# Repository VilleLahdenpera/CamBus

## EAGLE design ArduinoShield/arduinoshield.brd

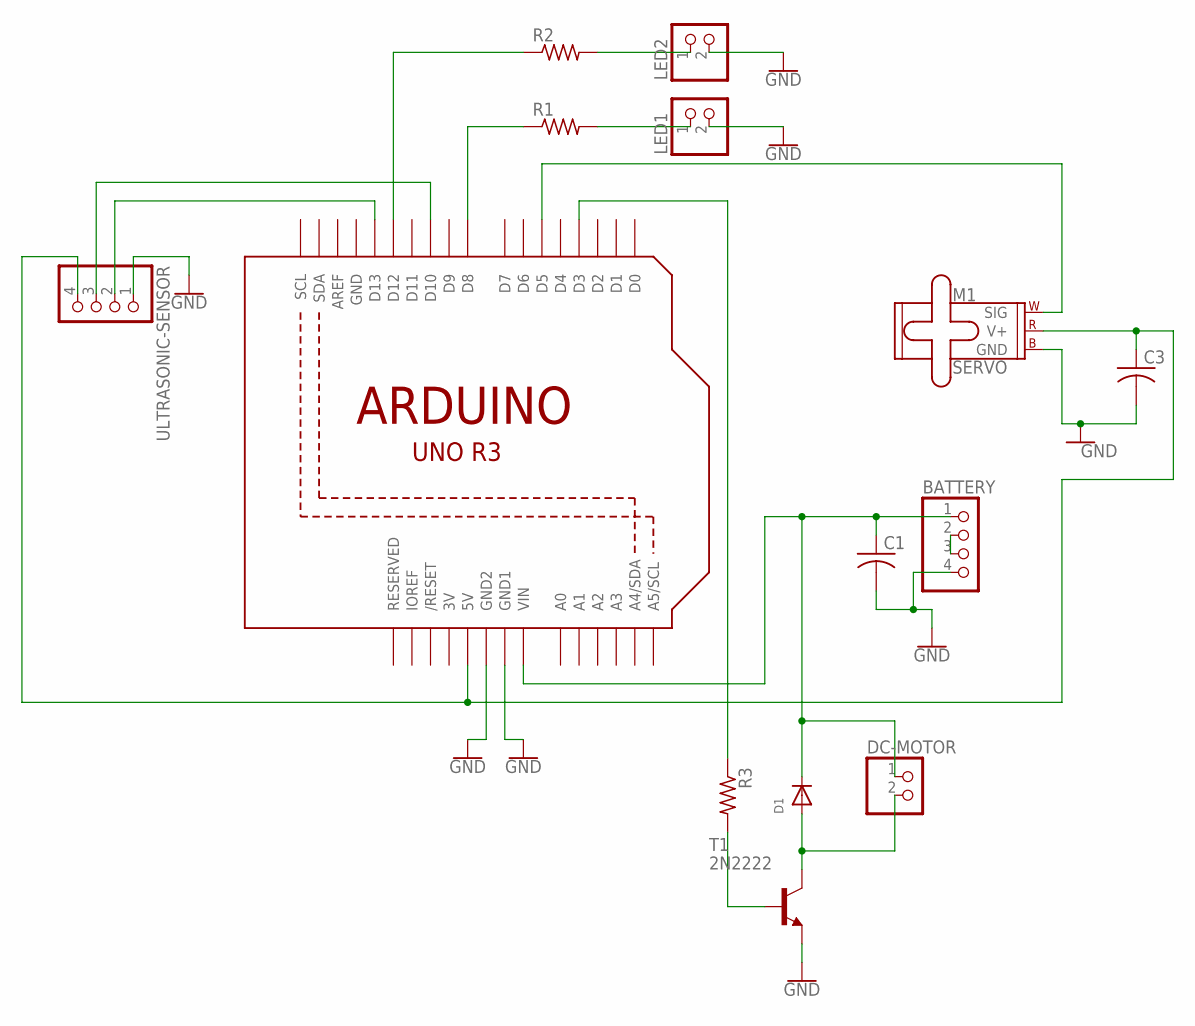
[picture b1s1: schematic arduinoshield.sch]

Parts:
BATTERY: PINHD-1X4; 1X04
C1, C3: C-US025-025X050; C025-025X050
D1: DIODEDO-1N4148; DO-1N4148
DC-MOTOR: PINHD-1X2; 1X02
LED1, LED2: PINHD-1X2; 1X02
M1: SERVO; 1X03
R1, R2, R3: R-US_0204/5; 0204/5
T1: 2N2222; TO92-EBC-OVAL
U1: ARDUINOR3-BPLACE
ULTRASONIC-SENSOR: PINHD-1X4; 1X04

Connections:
3V: U1.3V
GND: BATTERY.4, C1.2, C3.2, LED1.2, LED2.2, M1.3 (GND), T1.E, U1.GND, U1.GND1, U1.GND2, ULTRASONIC-SENSOR.1
MOOTTORI: C3.1, M1.2 (V+), U1.5V, ULTRASONIC-SENSOR.4
unnamed: R1.1, U1.D8
unnamed: LED1.1, R1.2
unnamed: M1.1 (SIG), U1.D5
unnamed: R2.1, U1.D12
unnamed: BATTERY.2, BATTERY.3
unnamed: LED2.1, R2.2
unnamed: U1.D13, ULTRASONIC-SENSOR.2
unnamed: U1.D10, ULTRASONIC-SENSOR.3
unnamed: R3.1, U1.D3
unnamed: R3.2, T1.B
unnamed: D1.A, DC-MOTOR.2, T1.C
unnamed: BATTERY.1, C1.1, D1.C, DC-MOTOR.1, U1.VIN

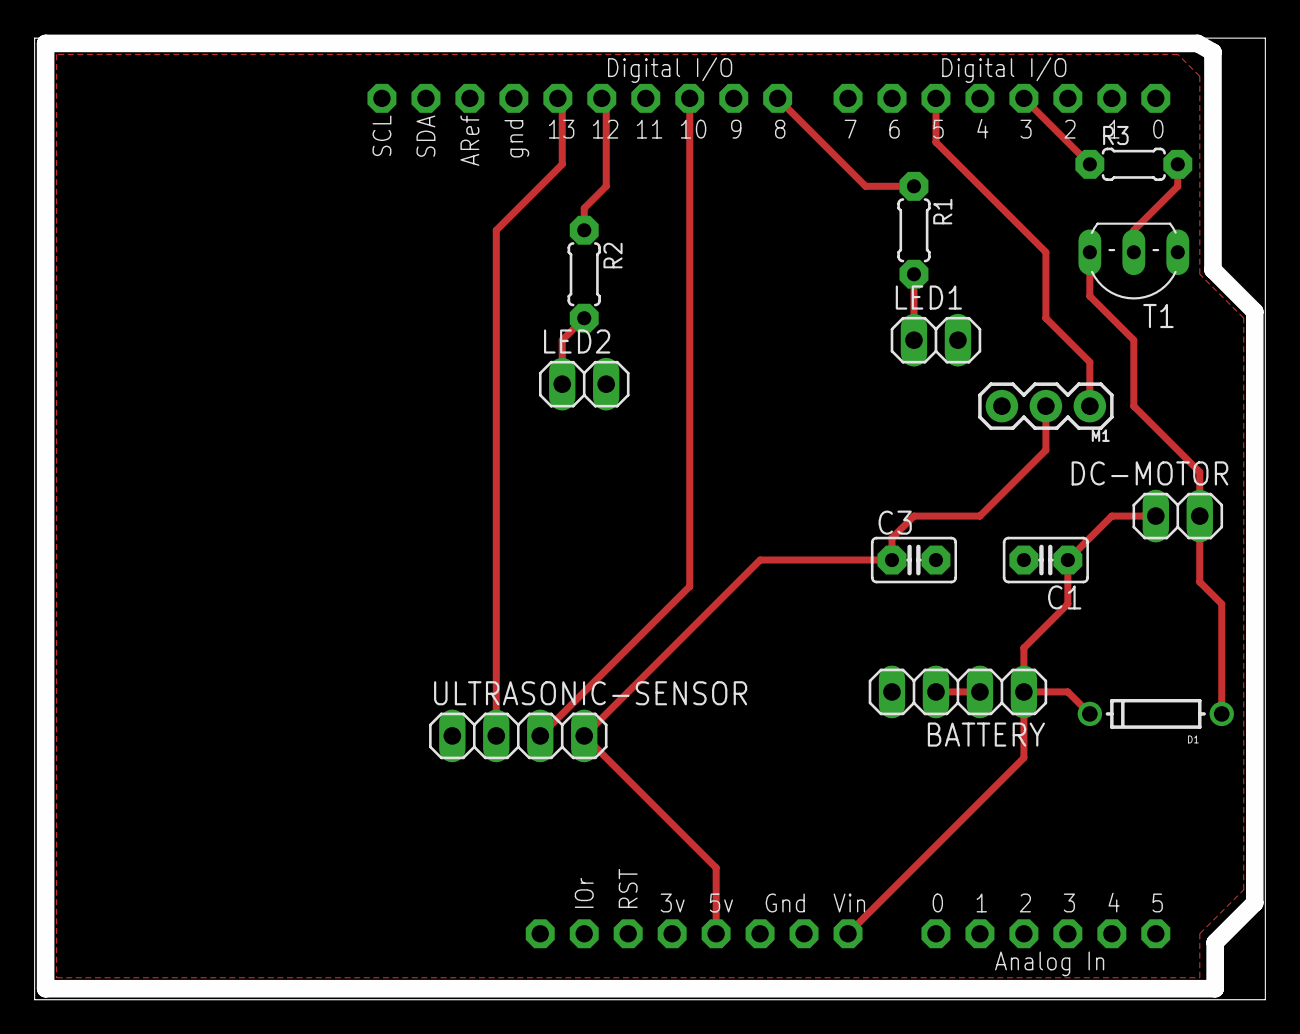
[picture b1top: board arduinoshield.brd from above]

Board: 2 copper layers, 70.1 x 54.7 mm, 14 parts (0 on the bottom side), 14 nets.

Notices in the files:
parts and their libraries:
SparkFun-Electromechanical: Licensing: Creative Commons ShareAlike 4.0 International - https://creativecommons.org/licenses/by-sa/4.0
